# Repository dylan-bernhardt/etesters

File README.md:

# etesters

## Presentation

A partir des fichiers de production (Gerber RS-274X), le package permet de sélectionner les points d'intérêts à garder pour la construction d'un banc de test.

## Install

Installer pip si ce n'est pas déjà fait
```
sudo apt-get install pip
```

Installer le module
```
git clone https://github.com/dxl0/etesters.git
cd etesters
pip install .
```

## Use

```
touch app.py
echo "import etesters" >> app.py
echo "etesters.App().display() >> app.py
python3 app.py
```

## Doc

La doc se trouve au format html dans [/docs/build/html/index.html](/docs/build/html) .

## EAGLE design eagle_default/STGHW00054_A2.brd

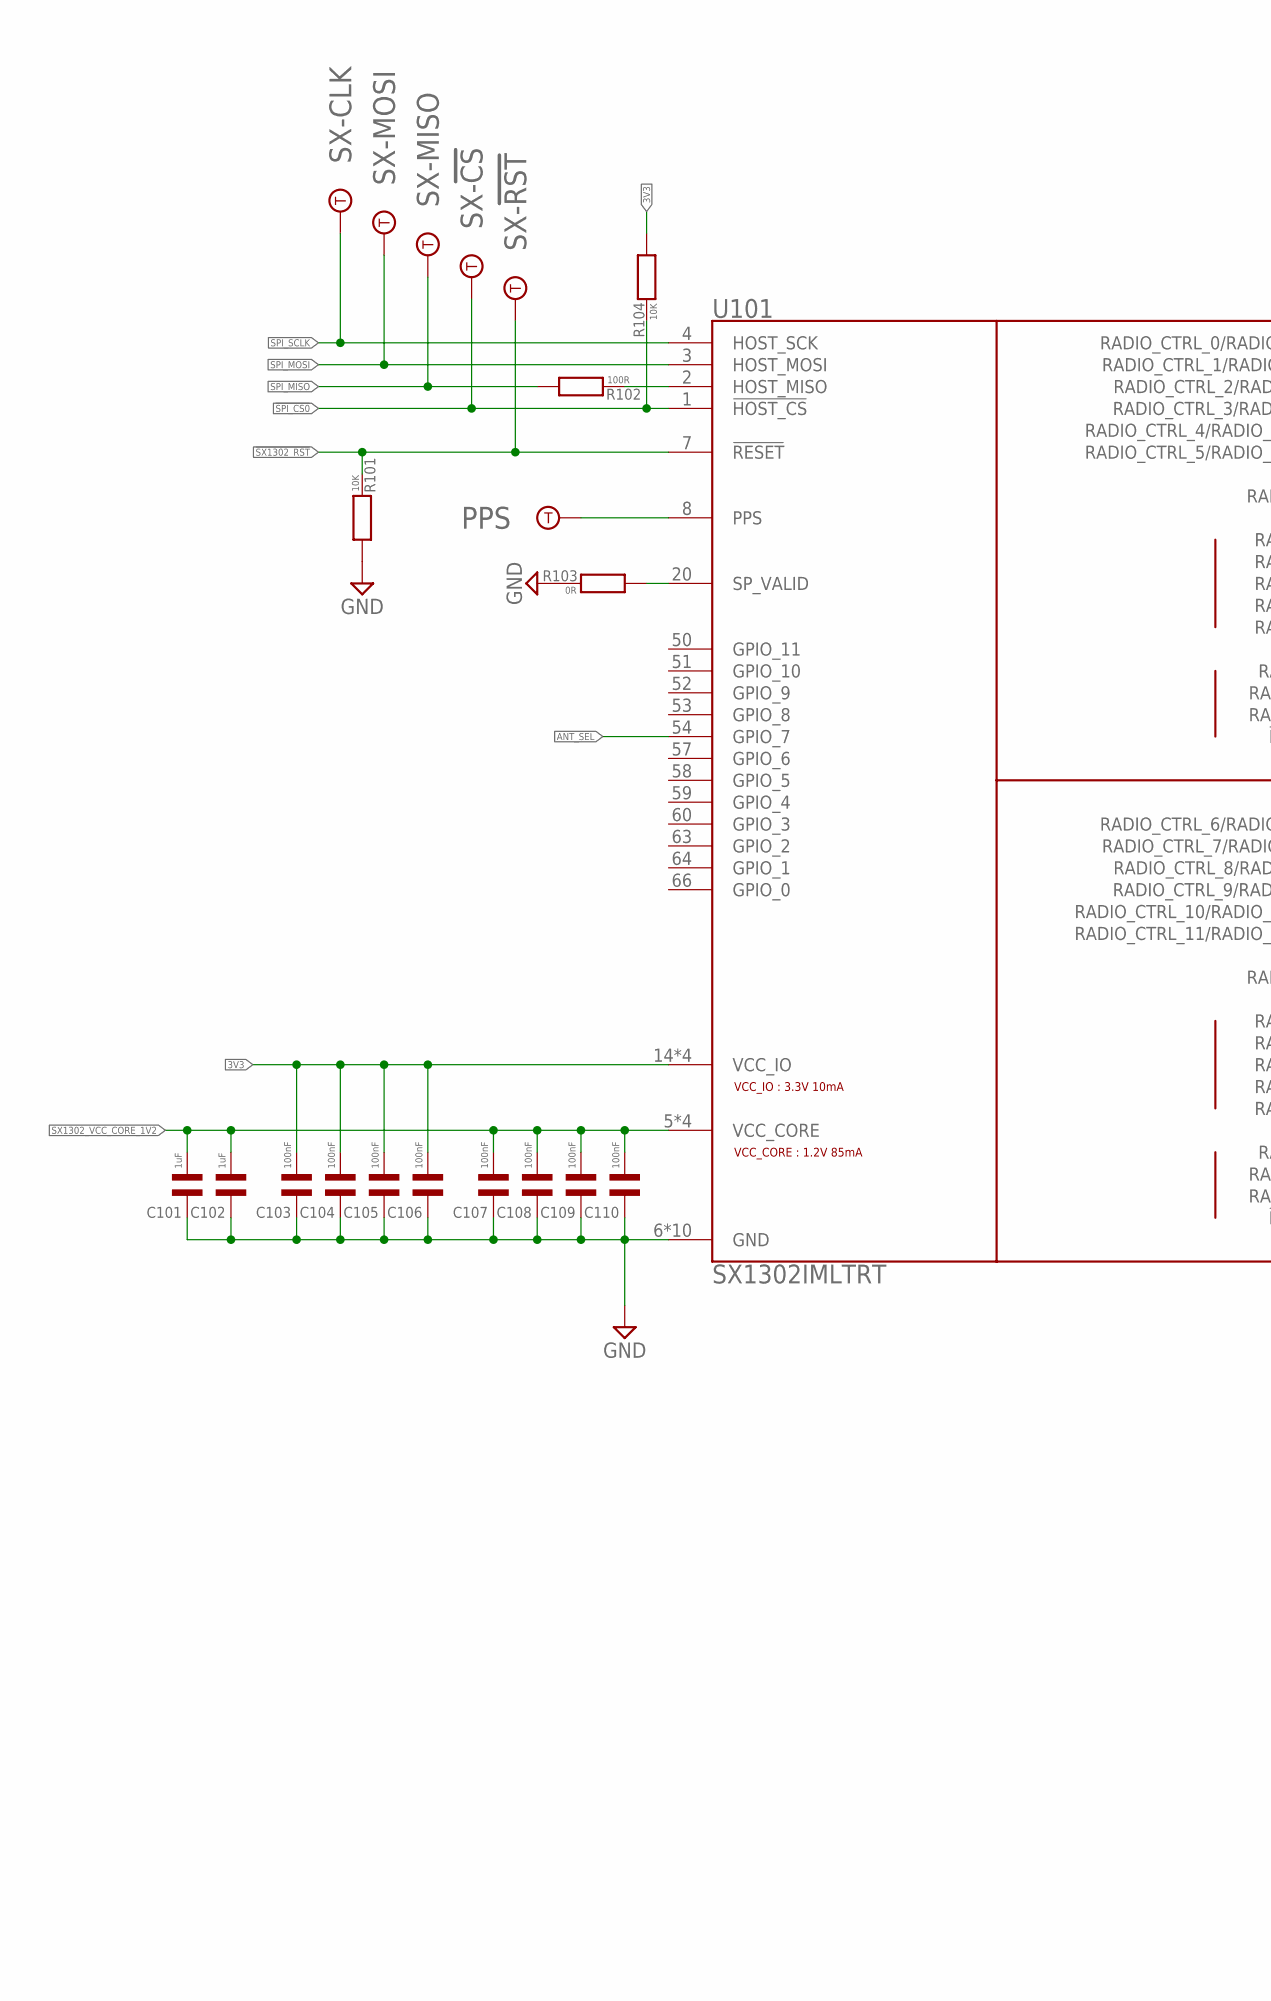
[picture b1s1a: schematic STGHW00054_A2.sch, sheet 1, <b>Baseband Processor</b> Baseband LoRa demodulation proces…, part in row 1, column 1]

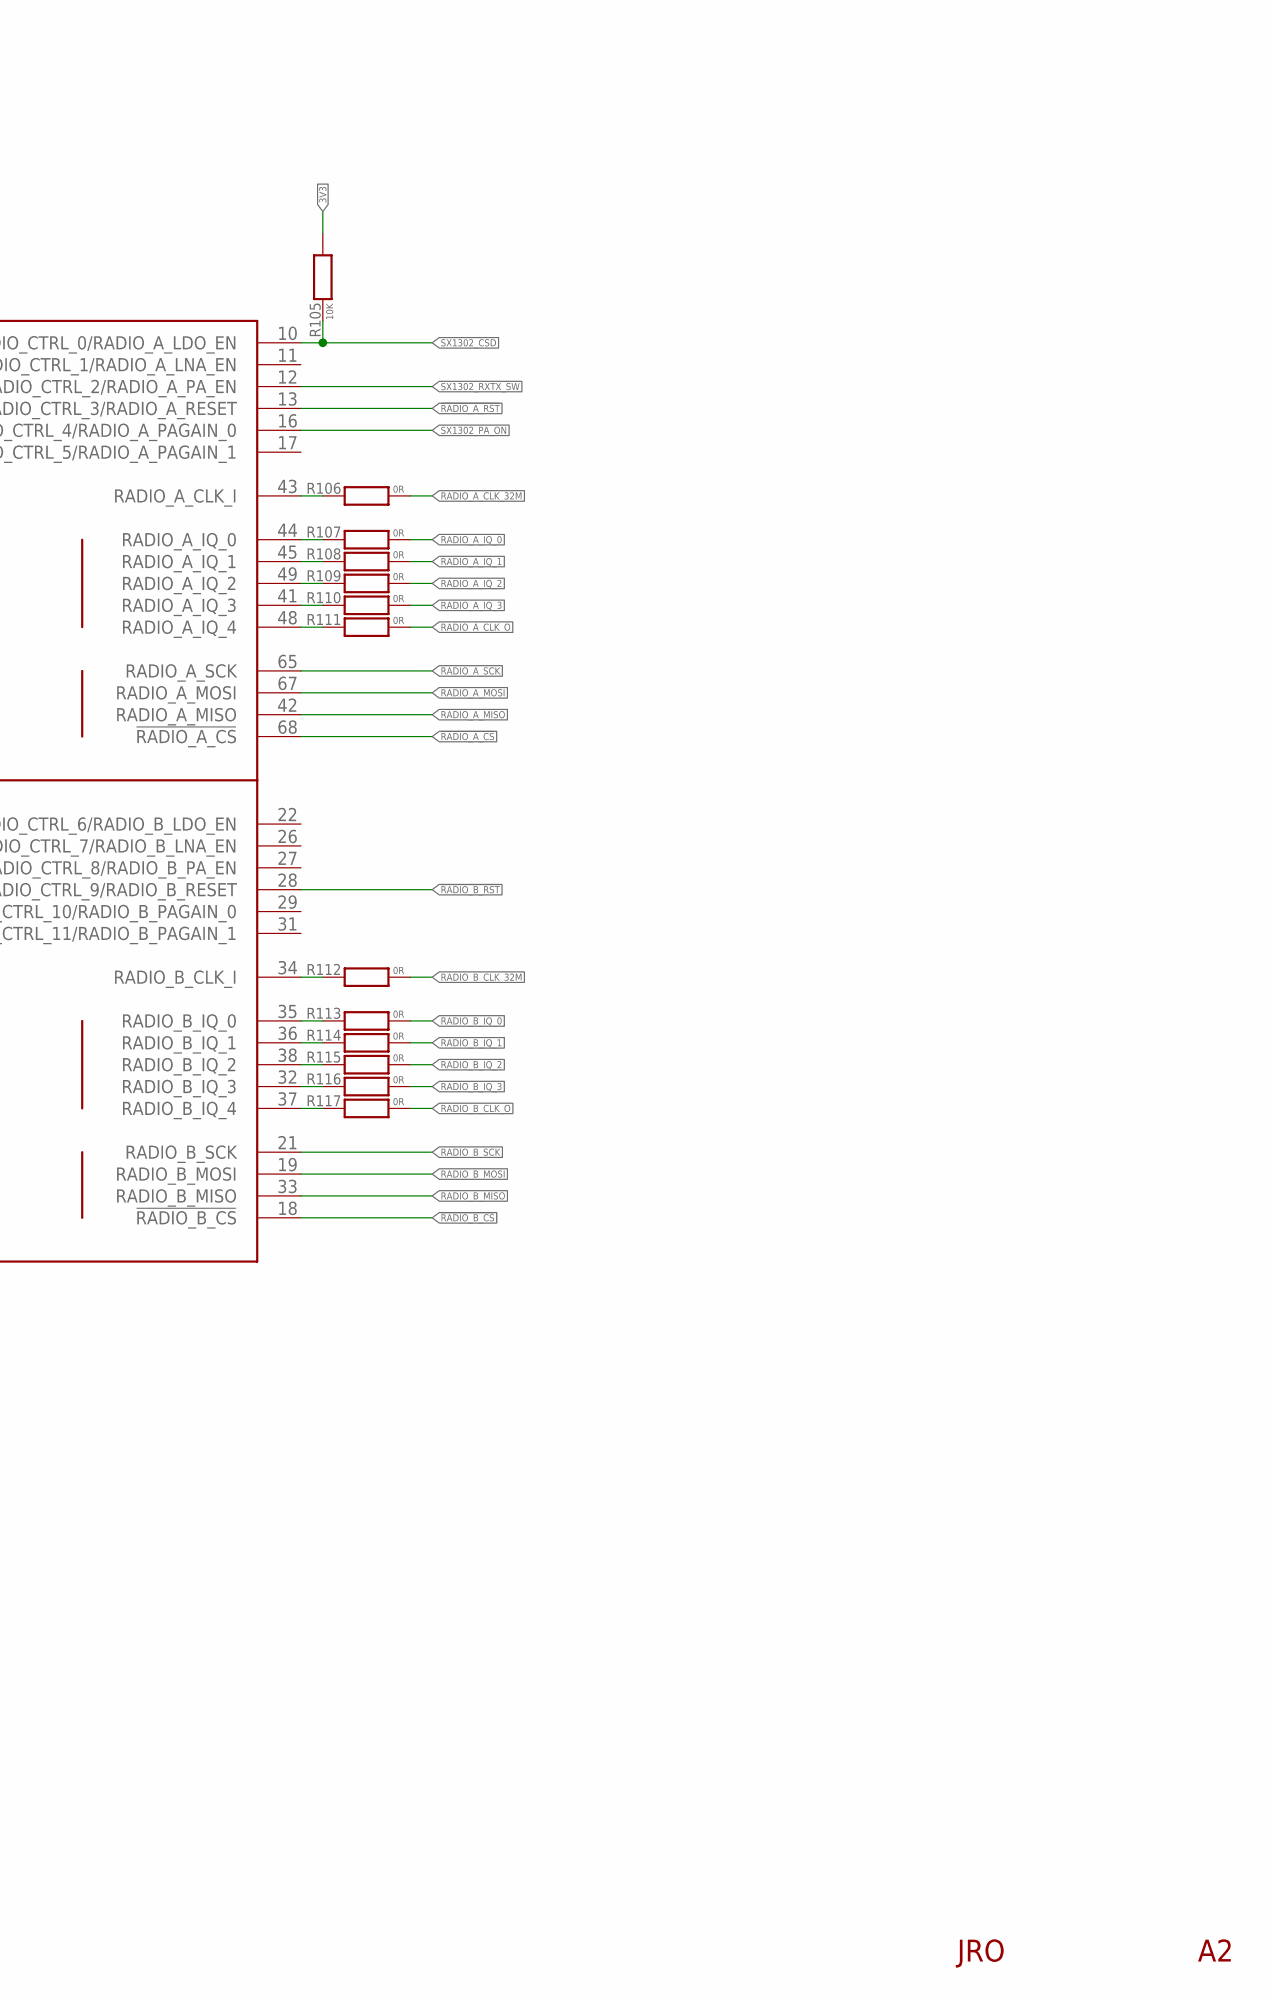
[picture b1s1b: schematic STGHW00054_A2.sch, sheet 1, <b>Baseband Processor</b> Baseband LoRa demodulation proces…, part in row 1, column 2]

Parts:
C101, C102: 1uF; C0402; MPN CL05A105KO5NNNC
C103, C104, C105, C106, C107, C108, C109, C110: 100nF; C0402; MPN CC0402KRX7R7BB104
PPS: TESPOINT-SMD1.5MM; TESTPOINT-1.5MM
R101, R104, R105: 10K; R0402; MPN RC0402JR-0710KL
R102: 100R; R0402; MPN RC0402JR-07100RL
R103, R106, R107, R108, R109, R110, R111, R112, R113, R114, R115, R116, R117: 0R; R0402; MPN RC0402JR-070RL
SX-!CS!: TESPOINT-SMD1.5MM; TESTPOINT-1.5MM
SX-!RST!: TESPOINT-SMD1.5MM; TESTPOINT-1.5MM
SX-CLK: TESPOINT-SMD1.5MM; TESTPOINT-1.5MM
SX-MISO: TESPOINT-SMD1.5MM; TESTPOINT-1.5MM
SX-MOSI: TESPOINT-SMD1.5MM; TESTPOINT-1.5MM
U101: SX1302IMLTRT; QFN35P700X700X80-69T556; MPN SX1302IMLTRT

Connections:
3V3: C103.2, C104.2, C105.2, C106.2, R104.1, R105.1, U101.14 (VCC_IO), U101.30 (VCC_IO), U101.47 (VCC_IO), U101.61 (VCC_IO); also elsewhere on the board
!RADIO_A_CS!: U101.68 (!RADIO_A_CS!); also elsewhere on the board
!RADIO_A_RST!: U101.13 (RADIO_CTRL_3/RADIO_A_RESET); also elsewhere on the board
!RADIO_B_CS!: U101.18 (!RADIO_B_CS!); also elsewhere on the board
!RADIO_B_RST!: U101.28 (RADIO_CTRL_9/RADIO_B_RESET); also elsewhere on the board
!SPI_CS0!: R104.2, SX-!CS!.1, U101.1 (!HOST_CS!); also elsewhere on the board
!SX1302_RST!: R101.2, SX-!RST!.1, U101.7 (!RESET!); also elsewhere on the board
ANT_SEL: U101.54 (GPIO_7); also elsewhere on the board
GND: C101.1, C102.1, C103.1, C104.1, C105.1, C106.1, C107.1, C108.1, C109.1, C110.1, R101.1, R103.2, U101.6 (GND), U101.9 (GND), U101.15 (GND), U101.24 (GND), U101.25 (GND), U101.39 (GND), U101.46 (GND), U101.55 (GND), U101.62 (GND), U101.69 (GND); also elsewhere on the board
GPS_PPS: PPS.1, U101.8 (PPS)
HOST_MISO: R102.2, U101.2 (HOST_MISO)
RADIO_ACLK_I: R106.2, U101.43 (RADIO_A_CLK_I)
RADIO_A_CLK_32M: R106.1; also elsewhere on the board
RADIO_A_CLK_O: R111.1; also elsewhere on the board
RADIO_A_IQ-0: R107.2, U101.44 (RADIO_A_IQ_0)
RADIO_A_IQ-1: R108.2, U101.45 (RADIO_A_IQ_1)
RADIO_A_IQ-2: R109.2, U101.49 (RADIO_A_IQ_2)
RADIO_A_IQ-3: R110.2, U101.41 (RADIO_A_IQ_3)
RADIO_A_IQ-4: R111.2, U101.48 (RADIO_A_IQ_4)
RADIO_A_IQ_0: R107.1; also elsewhere on the board
RADIO_A_IQ_1: R108.1; also elsewhere on the board
RADIO_A_IQ_2: R109.1; also elsewhere on the board
RADIO_A_IQ_3: R110.1; also elsewhere on the board
RADIO_A_MISO: U101.42 (RADIO_A_MISO); also elsewhere on the board
RADIO_A_MOSI: U101.67 (RADIO_A_MOSI); also elsewhere on the board
RADIO_A_SCK: U101.65 (RADIO_A_SCK); also elsewhere on the board
RADIO_B_CLK_32M: R112.1; also elsewhere on the board
RADIO_B_CLK_I: R112.2, U101.34 (RADIO_B_CLK_I)
RADIO_B_CLK_O: R117.1; also elsewhere on the board
RADIO_B_IQ-0: R113.2, U101.35 (RADIO_B_IQ_0)
RADIO_B_IQ-1: R114.2, U101.36 (RADIO_B_IQ_1)
RADIO_B_IQ-2: R115.2, U101.38 (RADIO_B_IQ_2)
RADIO_B_IQ-3: R116.2, U101.32 (RADIO_B_IQ_3)
RADIO_B_IQ-4: R117.2, U101.37 (RADIO_B_IQ_4)
RADIO_B_IQ_0: R113.1; also elsewhere on the board
RADIO_B_IQ_1: R114.1; also elsewhere on the board
RADIO_B_IQ_2: R115.1; also elsewhere on the board
RADIO_B_IQ_3: R116.1; also elsewhere on the board
RADIO_B_MISO: U101.33 (RADIO_B_MISO); also elsewhere on the board
RADIO_B_MOSI: U101.19 (RADIO_B_MOSI); also elsewhere on the board
RADIO_B_SCK: U101.21 (RADIO_B_SCK); also elsewhere on the board
SPI_MISO: R102.1, SX-MISO.1; also elsewhere on the board
SPI_MOSI: SX-MOSI.1, U101.3 (HOST_MOSI); also elsewhere on the board
SPI_SCLK: SX-CLK.1, U101.4 (HOST_SCK); also elsewhere on the board
SP_VALID: R103.1, U101.20 (SP_VALID)
SX1302_CSD: R105.2, U101.10 (RADIO_CTRL_0/RADIO_A_LDO_EN); also elsewhere on the board
SX1302_PA_ON: U101.16 (RADIO_CTRL_4/RADIO_A_PAGAIN_0); also elsewhere on the board
SX1302_RXTX_SW: U101.12 (RADIO_CTRL_2/RADIO_A_PA_EN); also elsewhere on the board
SX1302_VCC_CORE_1V2: C101.2, C102.2, C107.2, C108.2, C109.2, C110.2, U101.5 (VCC_CORE), U101.23 (VCC_CORE), U101.40 (VCC_CORE), U101.56 (VCC_CORE); also elsewhere on the board

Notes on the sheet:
JRO

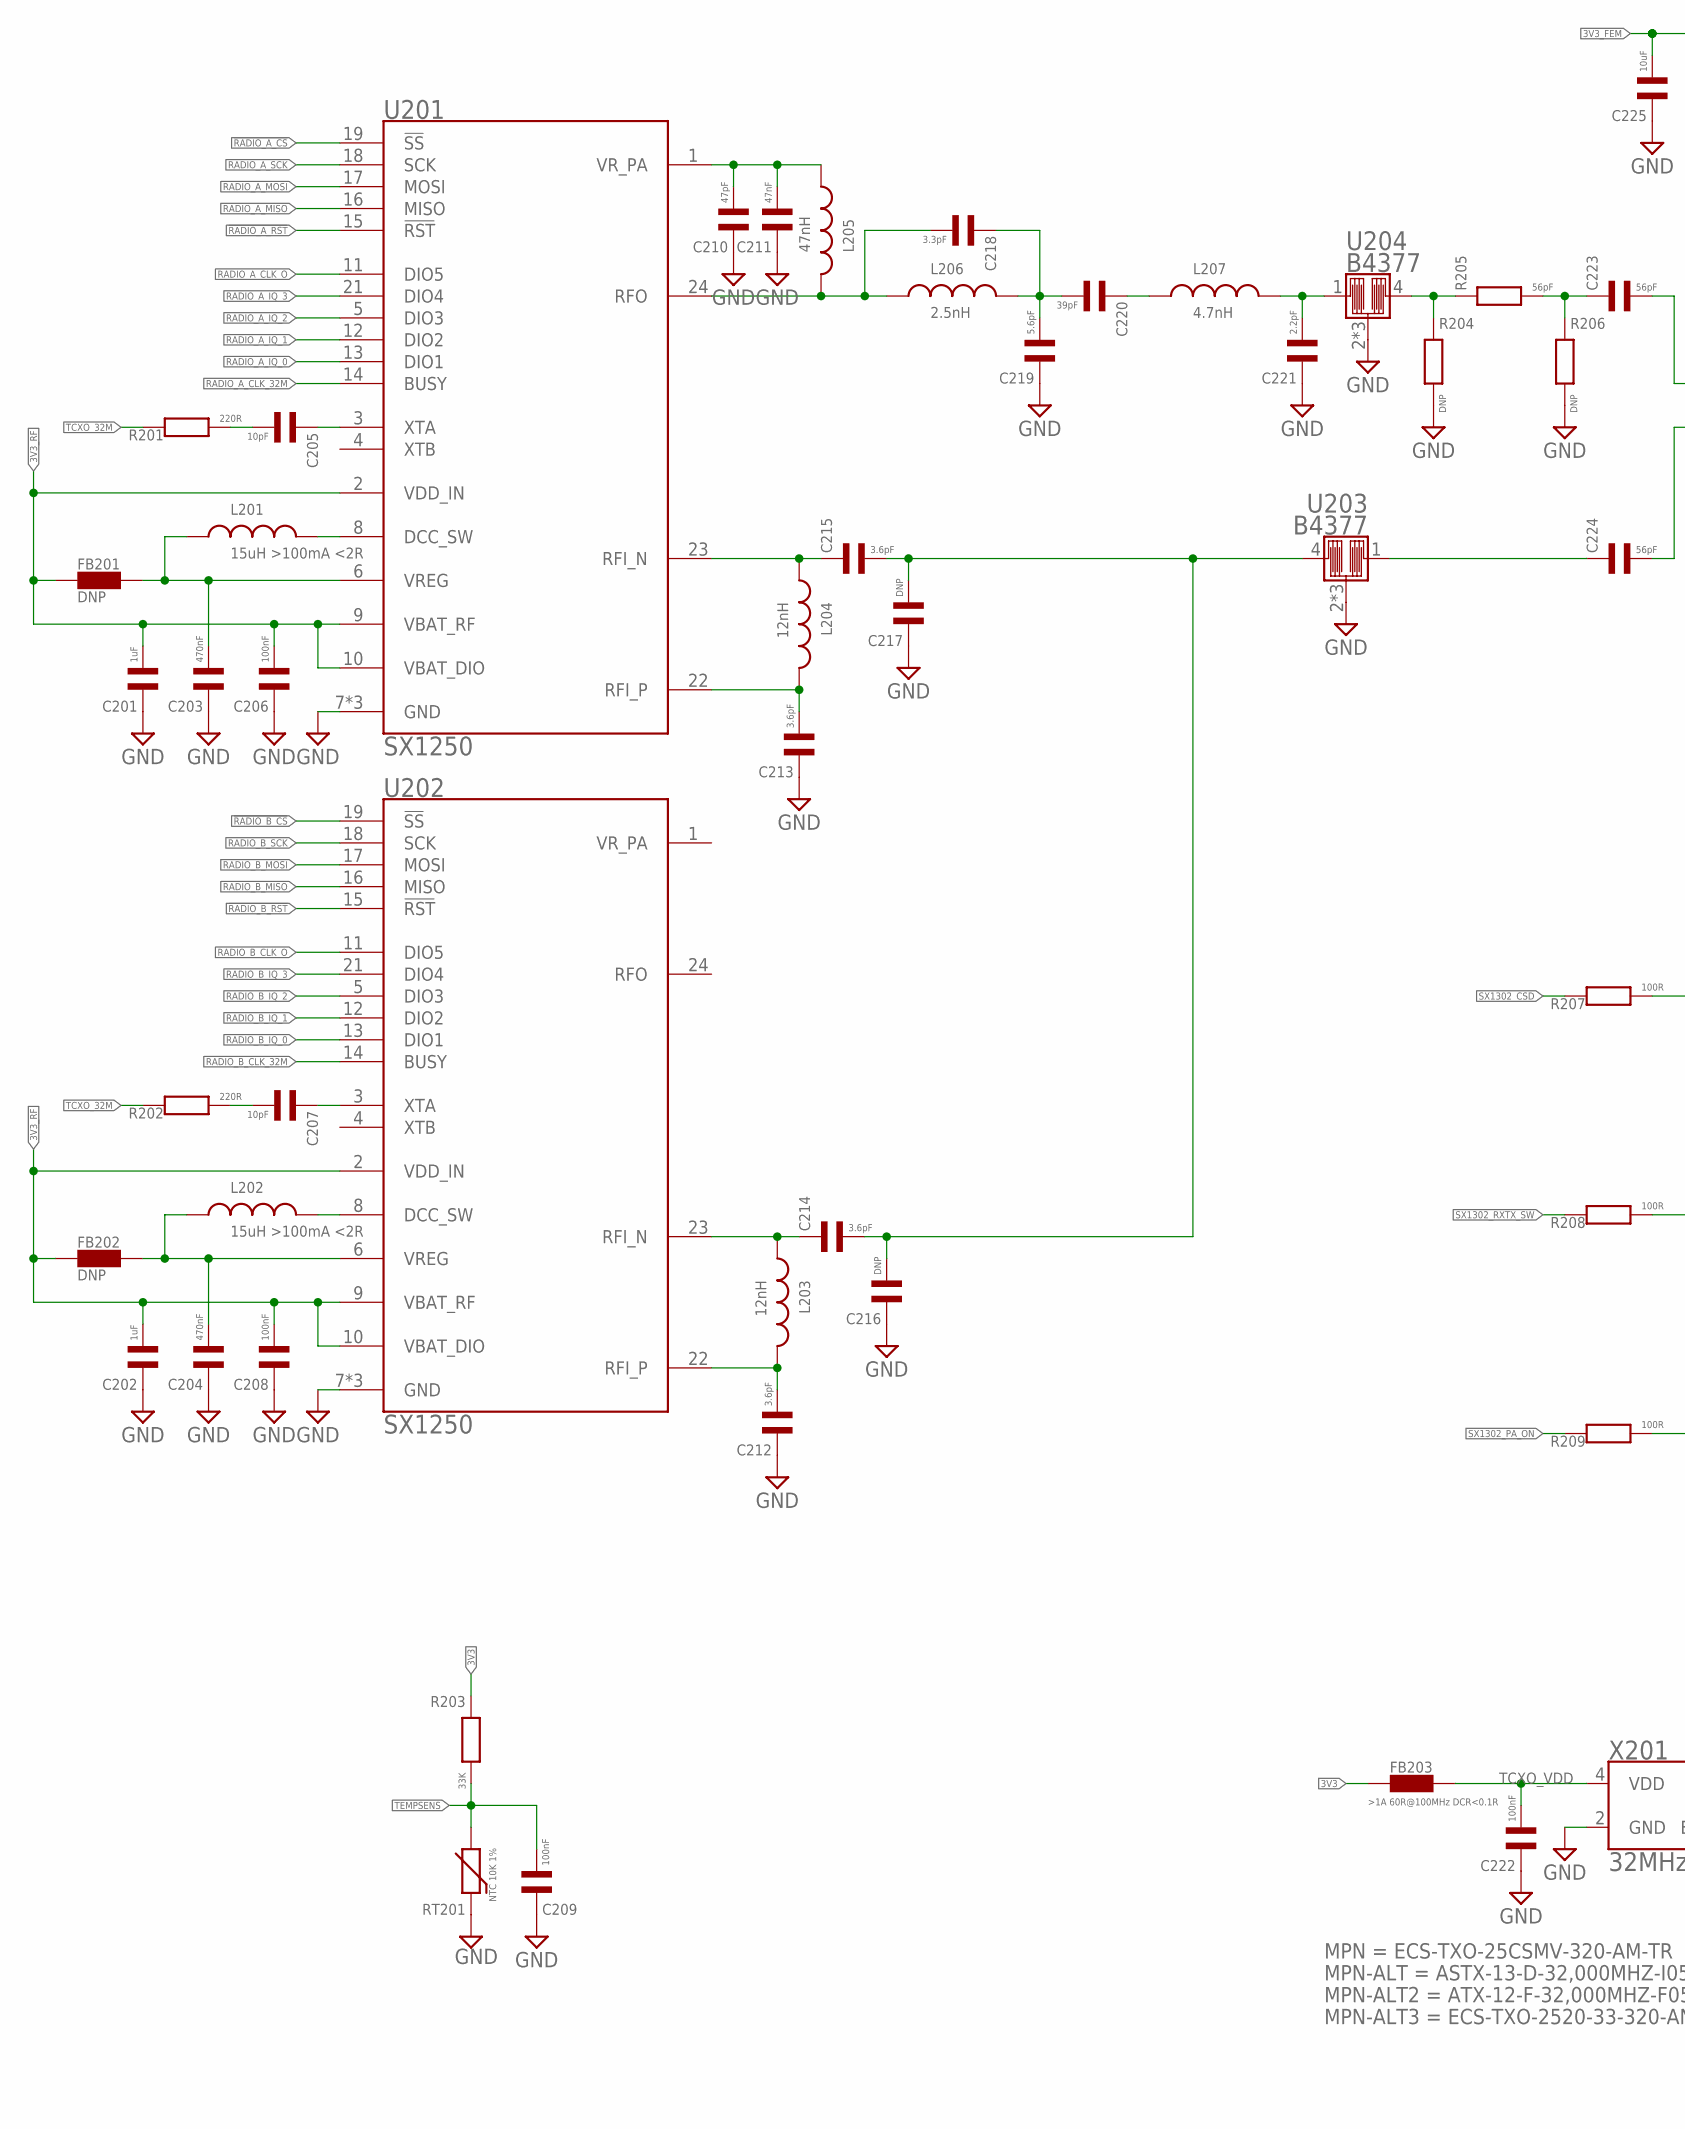
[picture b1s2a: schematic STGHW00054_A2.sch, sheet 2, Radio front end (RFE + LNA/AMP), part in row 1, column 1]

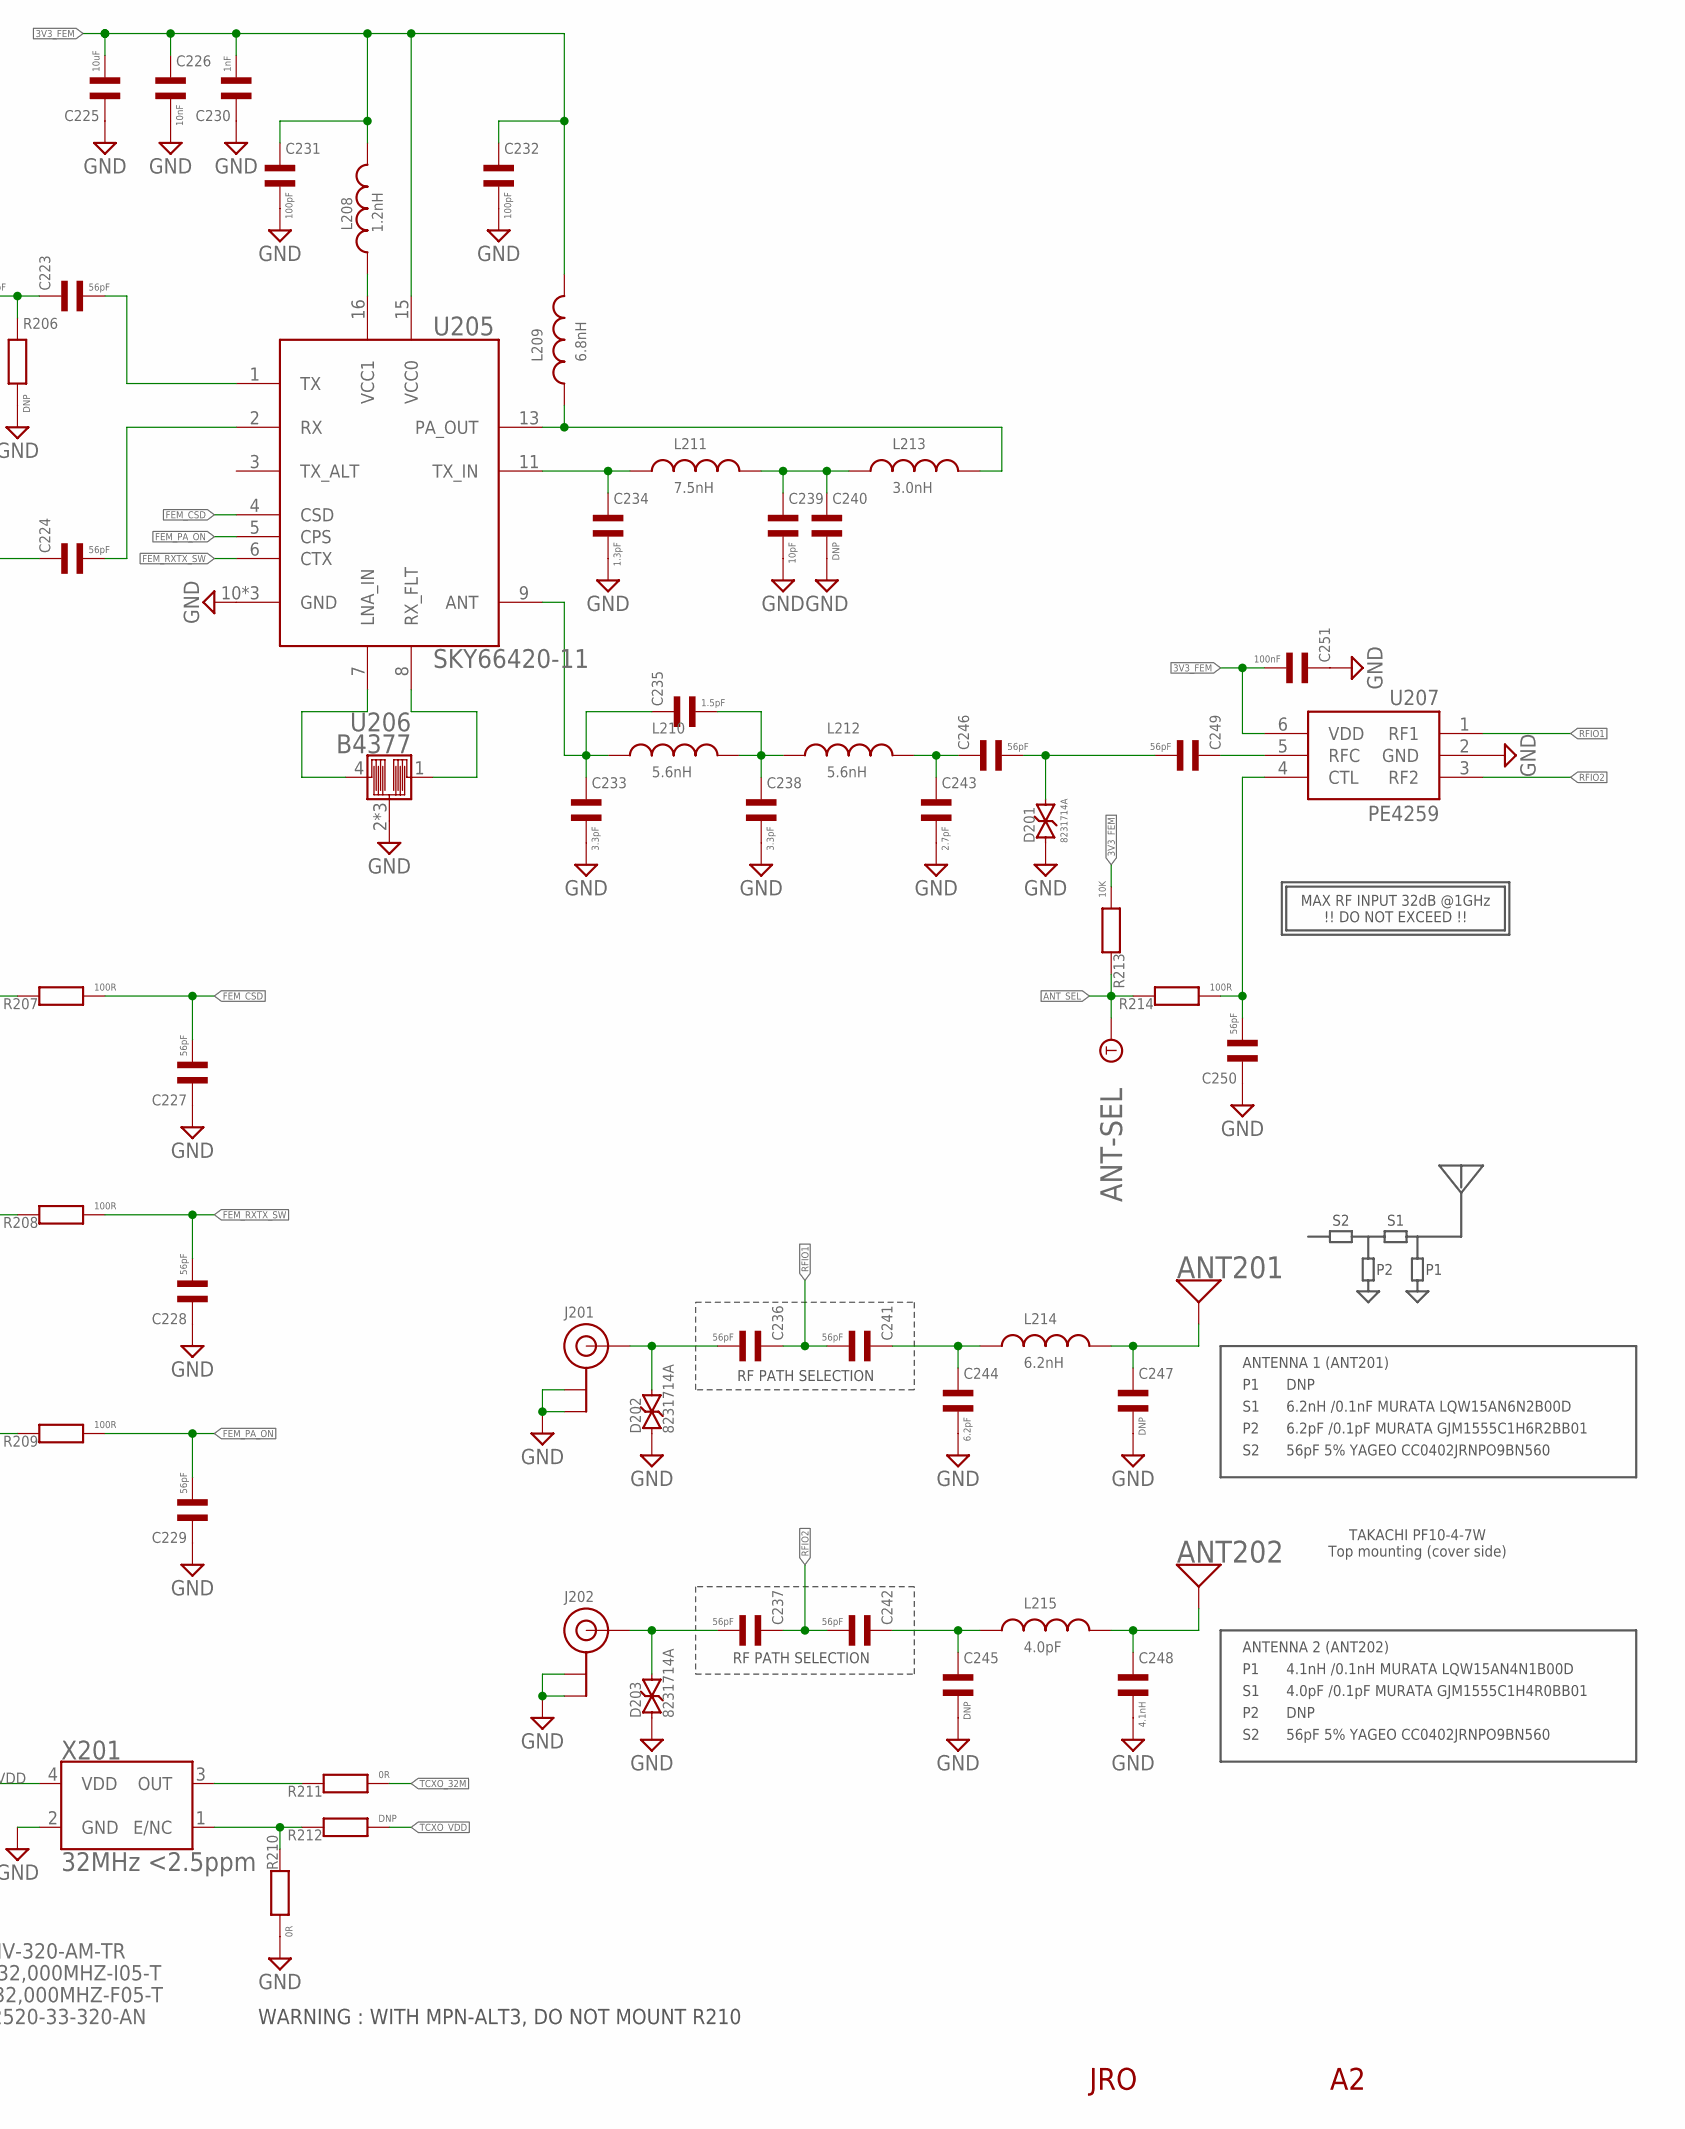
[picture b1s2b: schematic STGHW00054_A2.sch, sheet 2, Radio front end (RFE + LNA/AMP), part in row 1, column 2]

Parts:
ANT201: MLA-DN038; DN038
ANT202: MLA-DN038-MIRROR; DN038_MIRROR
ANT-SEL: TESPOINT-SMD1.5MM; TESTPOINT-1.5MM
C201, C202: 1uF; C0402; MPN CL05A105KO5NNNC
C203, C204: 470nF; C0603; MPN CL10B474KO8NNNC
C205, C207, C239: 10pF; C0402; MPN CC0402JRNPO9BN100
C206, C208, C209, C222, C251: 100nF; C0402; MPN CC0402KRX7R7BB104
C210: 47pF; C0402; MPN 0402N470F500CT
C211: 47nF; C0402; MPN 0402B473K250CT
C212, C213, C214, C215: 3.6pF; C0402; MPN GJM1555C1H3R6BB01D
C216, C217, C240, C245, C247: DNP; C0402
C218, C233, C238: 3.3pF; C0402; MPN GJM1555C1H3R3BB01D
C219: 5.6pF; C0402; MPN GJM1555C1H5R6BB01D
C220: 39pF; C0402; MPN GJM1555C1H390FB01D
C221: 2.2pF; C0402; MPN GJM1555C1H2R2BB01D
C223, C224, C227, C228, C229, C236, C237, C241, C242, C246, C249, C250: 56pF; C0402; MPN CC0402JRNPO9BN560
C225: 10uF; C0603; MPN CL10A106KP8NNNC
C226: 10nF; C0402; MPN CC0402KRX7R9BB103
C230: 1nF; C0402; MPN CC0402KRX7R9BB102
C231, C232: 100pF; C0402; MPN CC0402JRNPO9BN101
C234: 1.3pF; C0402; MPN GJM1555C1H1R3BB01D
C235: 1.5pF; C0402; MPN GJM1555C1H1R5BB01D
C243: 2.7pF; C0402; MPN GJM1555C1H2R7BB01D
C244: 6.2pF; C0402; MPN GJM1555C1H6R2BB01D
C248: 4.1nH; C0402; MPN LQW15AN4N1B00D
D201, D202, D203: 8231714A; TVS0402; MPN 8231714A
FB201, FB202: DNP; FB0402; MPN BLM15PD600SN1D
FB203: >1A 60R@100MHz DCR<0.1R; FB0402; MPN BLM15PD600SN1D
J201, J202: DNP; U.FL_AMPHENOL_RF_A-1JB; MPN U.FL-R-SMT-1(80)
L201, L202: 15uH >100mA <2R; L0805; MPN MLZ2012M150WT000
L203, L204: 12nH; L0402; MPN LQW15AN12NG00D
L205: 47nH; L0402; MPN LQW15AN47NG00D
L206: 2.5nH; L0402; MPN LQW15AN2N5C00D
L207: 4.7nH; L0402; MPN LQW15AN4N7C00D
L208: 1.2nH; L0402; MPN LQG15HS1N2B02D
L209: 6.8nH; L0402; MPN LQW15AN6N8G80D
L210, L212: 5.6nH; L0402; MPN LQW15AN5N6C10D
L211: 7.5nH; L0402; MPN LQW15AN7N5G00D
L213: 3.0nH; L0402; MPN LQW15AN3N0C80D
L214: 6.2nH; L0402; MPN LQW15AN6N2B00D
L215: 4.0pF; L0402; MPN GJM1555C1H4R0BB01D
R201, R202: 220R; R0402; MPN 0402WGF2200TCE
R203: 33K; R0402; MPN RC0402JR-0710KL
R204, R206: DNP; R0402
R205: 56pF; R0402; MPN CC0402JRNPO9BN560
R207, R208, R209, R214: 100R; R0402; MPN RC0402JR-07100RL
R210, R211: 0R; R0402; MPN RC0402JR-070RL
R212: DNP; R0402; MPN RC0402JR-070RL
R213: 10K; R0402; MPN RC0402JR-0710KL
RT201: NTC 10K 1%; R0402; MPN NCP15XH103F03RC
U201, U202: SX1250; QFN50P400X400X100-25T270; MPN SX1250IMLTRT
U203, U204, U206: B4377; MPN B39871B4377P810
U205: SKY66420-11; QFN50P300X300X80-17T170; MPN SKY66420-11
U207: PE4259; SC70-6; MPN PE4259-63
X201: 32MHz <2.5ppm; OSCCC250X200X90N; MPN ECS-TXO-25CSMV-320-AM-TR

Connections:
3V3: FB203.1, R203.1; also elsewhere on the board
3V3_FEM: C225.2, C226.1, C230.2, C231.1, C232.1, C251.2, L208.2, L209.2, R213.2, U205.15 (VCC0), U207.6 (VDD); also elsewhere on the board
3V3_RF: C201.2, C202.2, C206.2, C208.2, FB201.1, FB202.1, U201.2 (VDD_IN), U201.9 (VBAT_RF), U201.10 (VBAT_DIO), U202.2 (VDD_IN), U202.9 (VBAT_RF), U202.10 (VBAT_DIO); also elsewhere on the board
!RADIO_A_CS!: U201.19 (!SS!); also elsewhere on the board
!RADIO_A_RST!: U201.15 (!RST!); also elsewhere on the board
!RADIO_B_CS!: U202.19 (!SS!); also elsewhere on the board
!RADIO_B_RST!: U202.15 (!RST!); also elsewhere on the board
ANT1: ANT201.FEED, C247.1, L214.2
ANT1_MATCH: C241.1, C244.1, L214.1
ANT2: ANT202.FEED, C248.1, L215.2
ANT2_MATCH: C242.1, C245.1, L215.1
ANT_CTL: C250.2, R214.2, U207.4 (CTL)
ANT_SEL: ANT-SEL.1, R213.1, R214.1; also elsewhere on the board
DCC_SW_RADIO_A: L201.2, U201.8 (DCC_SW)
DCC_SW_RADIO_B: L202.2, U202.8 (DCC_SW)
FEM_CSD: C227.2, R207.2, U205.4 (CSD)
FEM_PA_ON: C229.2, R209.2, U205.5 (CPS)
FEM_RXTX_SW: C228.2, R208.2, U205.6 (CTX)
GND: C201.1, C202.1, C203.1, C204.1, C206.1, C208.1, C209.1, C210.1, C211.1, C212.1, C213.1, C216.1, C217.1, C219.1, C221.1, C222.1, C225.1, C226.2, C227.1, C228.1, C229.1, C230.1, C231.2, C232.2, C233.2, C234.2, C238.2, C239.2, C240.2, C243.2, C244.2, C245.2, C247.2, C248.2, C250.1, C251.1, D201.1, D202.1, D203.1, J201.1@GND (GND), J201.2@GND (GND), J201.GND, J202.1@GND (GND), J202.2@GND (GND), J202.GND, R204.2, R206.2, R210.2, RT201.1, U201.7 (GND), U201.20 (GND), U201.25 (GND), U202.7 (GND), U202.20 (GND), U202.25 (GND), U203.2 (GND), U203.3 (GND), U203.5 (GND), U204.2 (GND), U204.3 (GND), U204.5 (GND), U205.10 (GND), U205.12 (GND), U205.17 (GND), U206.2 (GND), U206.3 (GND), U206.5 (GND), U207.2 (GND), X201.2 (GND); also elsewhere on the board
LNA_FLTR_IN: U205.7 (LNA_IN), U206.4 (OUT)
unnamed: C205.2, R201.2
unnamed: C207.2, R202.2
PAS_OUTèFLTR: C239.1, C240.1, L211.2, L213.1
PA_OUT: L209.1, L213.2, U205.13 (PA_OUT)
RADIO_A_CLK_32M: U201.14 (BUSY); also elsewhere on the board
RADIO_A_CLK_O: U201.11 (DIO5); also elsewhere on the board
RADIO_A_IQ_0: U201.13 (DIO1); also elsewhere on the board
RADIO_A_IQ_1: U201.12 (DIO2); also elsewhere on the board
RADIO_A_IQ_2: U201.5 (DIO3); also elsewhere on the board
RADIO_A_IQ_3: U201.21 (DIO4); also elsewhere on the board
RADIO_A_MISO: U201.16 (MISO); also elsewhere on the board
RADIO_A_MOSI: U201.17 (MOSI); also elsewhere on the board
RADIO_A_SCK: U201.18 (SCK); also elsewhere on the board
RADIO_B_CLK_32M: U202.14 (BUSY); also elsewhere on the board
RADIO_B_CLK_O: U202.11 (DIO5); also elsewhere on the board
RADIO_B_IQ_0: U202.13 (DIO1); also elsewhere on the board
RADIO_B_IQ_1: U202.12 (DIO2); also elsewhere on the board
RADIO_B_IQ_2: U202.5 (DIO3); also elsewhere on the board
RADIO_B_IQ_3: U202.21 (DIO4); also elsewhere on the board
RADIO_B_MISO: U202.16 (MISO); also elsewhere on the board
RADIO_B_MOSI: U202.17 (MOSI); also elsewhere on the board
RADIO_B_SCK: U202.18 (SCK); also elsewhere on the board
RFIO1: C236.1, C241.2, U207.1 (RF1)
RFIO2: C237.1, C242.2, U207.3 (RF2)
RFI_FLTR: C214.2, C215.2, C216.2, C217.2, U203.4 (OUT)
RFI_N_RADIO_A: C215.1, L204.1, U201.23 (RFI_N)
RFI_N_RADIO_B: C214.1, L203.1, U202.23 (RFI_N)
RFI_P_RADIO_A: C213.2, L204.2, U201.22 (RFI_P)
RFI_P_RADIO_B: C212.2, L203.2, U202.22 (RFI_P)
RFI_RX: C224.2, U205.2 (RX)
RFI_RX_DCBLK: C224.1, U203.1 (IN)
RFO_FLTR: C218.1, C219.2, C220.2, L206.2
RFO_FLTR_1: C220.1, L207.1
RFO_FLTR_2: C221.2, L207.2, U204.1 (IN)
RFO_RADIO_A: C218.2, L205.1, L206.1, U201.24 (RFO)
RFO_TX: C223.2, U205.1 (TX)
RFO_TX_DCBLK: C223.1, R205.2, R206.1
RFO_TX_FLTR: R204.1, R205.1, U204.4 (OUT)
RX_OUT_FLTR: U205.8 (RX_FLT), U206.1 (IN)
SX1302_CSD: R207.1; also elsewhere on the board
SX1302_PA_ON: R209.1; also elsewhere on the board
SX1302_RXTX_SW: R208.1; also elsewhere on the board
TCXO_32M: R201.1, R202.1, R211.2
TCXO_EN: R210.1, R212.1, X201.1 (E/NC)
TCXO_OUT: R211.1, X201.3 (OUT)
TCXO_VDD: C222.2, FB203.2, R212.2, X201.4 (VDD)
TEMPSENS: C209.2, R203.2, RT201.2; also elsewhere on the board
TRX_DCBLK: C246.2, C249.2, D201.2
TRX_FLTR: C235.2, C238.1, L210.2, L212.1
TRX_FLTR_1: C243.1, C246.1, L212.2
TRX_PA: C233.1, C235.1, L210.1, U205.9 (ANT)
TRX_RF: C249.1, U207.5 (RFC)
TX_IN: C234.1, L211.1, U205.11 (TX_IN)
UFL1: C236.2, D202.2, J201.ANT (SIGNAL)
UFL2: C237.2, D203.2, J202.ANT (SIGNAL)
VCC1_PA: L208.1, U205.16 (VCC1)
VREG_RADIO_A: C203.2, FB201.2, L201.1, U201.6 (VREG)
VREG_RADIO_B: C204.2, FB202.2, L202.1, U202.6 (VREG)
VR_PA_RADIO_A: C210.2, C211.2, L205.2, U201.1 (VR_PA)
XTA_RADIO_A: C205.1, U201.3 (XTA)
XTA_RADIO_B: C207.1, U202.3 (XTA)

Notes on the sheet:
RF PATH SELECTION
MAX RF INPUT 32dB @1GHz !! DO NOT EXCEED !!
TAKACHI PF10-4-7W Top mounting (cover side)
ANTENNA 1 (ANT201)
ANTENNA 2 (ANT202)
DNP
6.2nH /0.1nF MURATA LQW15AN6N2B00D
6.2pF /0.1pF MURATA GJM1555C1H6R2BB01
56pF 5% YAGEO CC0402JRNPO9BN560
4.1nH /0.1nH MURATA LQW15AN4N1B00D
4.0pF /0.1pF MURATA GJM1555C1H4R0BB01
JRO
WARNING : WITH MPN-ALT3, DO NOT MOUNT R210

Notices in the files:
parts and their libraries:
TagConnect_stg: ©2009 ROFA.cz - modified and updated by Robert Darlington ‹rdarlington@gmail.com›
